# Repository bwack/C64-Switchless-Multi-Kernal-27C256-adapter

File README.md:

[![Badge License]][License]

<br>

![Logo]

<br>

<div align = center>

***A C64 + Disk Drives Switch-less Multi*** <br>
***Kernel ROM Adapter / Switcher***

<br>

---

[![Button Playlist]][Playlist]   
[![Button OSHPark]][OSHPark]   
[![Button Forum]][Forum]

[![Button Usage]][Usage]  
[![Button Develop]][Develop]  
[![Button Changelog]][Changelog]

---

<br>
<br>

<br>

## Supported Devices

![C64]  ![C64C]  ![1541]  ![1541C]  ![1541-II] 

<br>

</div>
  
<br>

## Boards

### Long

The  `longboard`  is designed for <br>
the  <kbd> C64 </kbd>  **+**  <kbd> 1541 </kbd>  **/**  <kbd> 1541Late </kbd>

<br>

### Short

The  `shortboard`  is designed for <br>
the  <kbd> C64C </kbd>  **+**  <kbd> 1541C </kbd>  **/**  <kbd> 1541-II </kbd>

<br>

### Note

*The innards of  `C64`  /  `C64C`  and  `1541`  /  `1541C`* <br>
*are often mixed together, and you must check their* <br>
*cases to be sure which boards they have.*

<br>
<br>

## Acknowledgment

### Based On   [<kbd> Sven Petersen </kbd>][Petersen]

*[C64 Kernal Adaptor Switch Shortboard]*

### Old Version   [<kbd> DiscoHR </kbd>][DiscoHR]

*[C64C C128 Multikernal Adapter]*

*It is possible to reused the original LED / Cable assembly.*

### Idea From   [<kbd> Tebl </kbd>][DiscoHR]

*[C64 Kernal Switcher]*

<br>

<!----------------------------------------------------------------------------->

[Playlist]: https://www.youtube.com/playlist?list=PLtQOf_JULmrQTB7486X5pXG1Aaxbl_RdE
[OSHPark]: https://oshpark.com/profiles/bwack 'Order The Board'
[Forum]: http://www.lemon64.com/forum/viewtopic.php?p=747333 'Lemon64 Forum Post'

[Changelog]: Documentation/Changelog.md
[Develop]: Documentation/Develop.md
[License]: LICENSE
[Usage]: Documentation/Usage.md
[Logo]: User%20Guide/media/SKS64-Logos-Ver2.png

[Badge License]: https://img.shields.io/badge/Open_Hardware-1.2-292961?style=for-the-badge

<!--------------------------------{ Devices }---------------------------------->

[1541-II]: https://img.shields.io/badge/１５４１－ＩＩ-d7cdbb?style=flat
[1541C]: https://img.shields.io/badge/１５４１Ｃ-d7cdbb?style=flat
[1541]: https://img.shields.io/badge/１５４１-d7cdbb?style=flat
[C64C]: https://img.shields.io/badge/Ｃ６４Ｃ-d7cdbb?style=flat
[C64]: https://img.shields.io/badge/Ｃ６４-d7cdbb?style=flat

<!----------------------------{ Acknowledgment }------------------------------->

[C64 Kernal Adaptor Switch Shortboard]: https://github.com/svenpetersen1965/C64-Kernal-Adaptor-Switch-short-board-
[C64C C128 Multikernal Adapter]: https://github.com/discoHR/C64C-C128-multikernal-adapter
[C64 Kernal Switcher]: https://github.com/tebl/C64-Kernal-Switcher

[Petersen]: https://github.com/svenpetersen1965
[DiscoHR]: https://github.com/discoHR
[Tebl]: https://github.com/tebl

<!--------------------------------{ Buttons }---------------------------------->

[Button Changelog]: https://img.shields.io/badge/Changelog-19abdd?style=for-the-badge&logoColor=white&logo=AzureArtifacts
[Button Playlist]: https://img.shields.io/badge/Playlist-FF0000?style=for-the-badge&logoColor=white&logo=Youtube
[Button Develop]: https://img.shields.io/badge/Develop-00979D?style=for-the-badge&logoColor=white&logo=Arduino
[Button OSHPark]: https://img.shields.io/badge/OSHPark-752c8d?style=for-the-badge&logoColor=white&logo=Houzz
[Button Usage]: https://img.shields.io/badge/Usage-ED145B?style=for-the-badge&logoColor=white&logo=AppleArcade
[Button Forum]: https://img.shields.io/badge/Forum-5287B8?style=for-the-badge&logoColor=white&logo=AskUbuntu

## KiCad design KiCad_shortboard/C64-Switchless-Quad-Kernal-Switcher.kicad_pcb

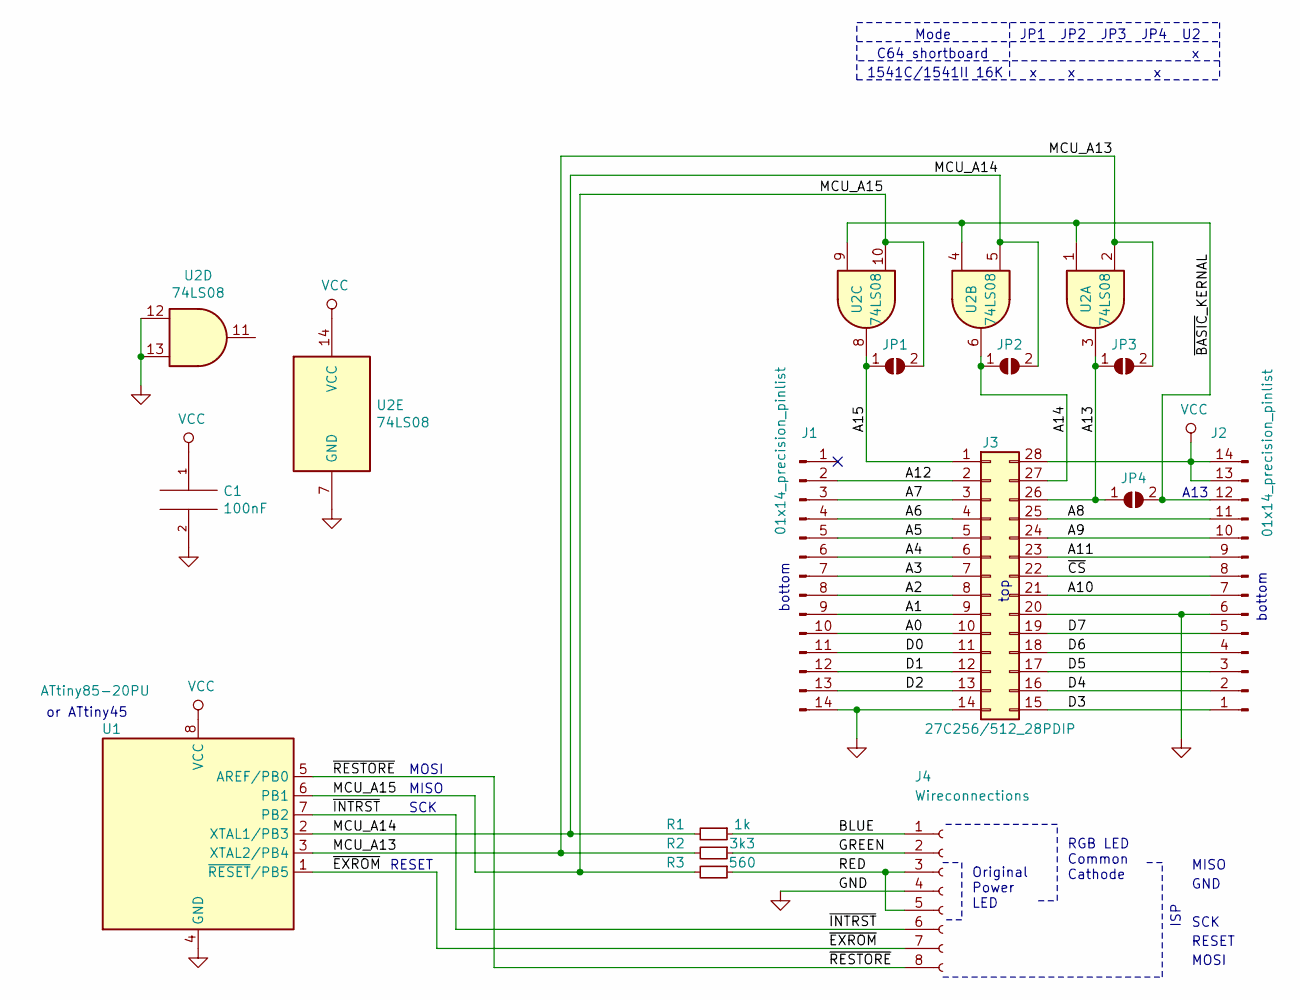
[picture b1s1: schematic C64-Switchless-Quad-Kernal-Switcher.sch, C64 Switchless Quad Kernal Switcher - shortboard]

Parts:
C1: 100nF; R_0805_2012Metric_Pad1.15x1.40mm_HandSolder
J1, J2: 01x14_precision_pinlist; PinHeader_1x14_P2.54mm_Vertical
J3: 27C256/512_28PDIP; DIP-28_W15.24mm_Socket
J4: Wireconnections; PinHeader_1x08_P2.54mm_Horizontal
JP1, JP2, JP3, JP4: SolderJumper_2_Open; J_0402
R1: 1k; R_0805_2012Metric_Pad1.15x1.40mm_HandSolder
R2: 3k3; R_0805_2012Metric_Pad1.15x1.40mm_HandSolder
R3: 560; R_0805_2012Metric_Pad1.15x1.40mm_HandSolder
U1: ATtiny85-20PU; DIP-8_W7.62mm_Socket
U2: 74LS08; SOIC-14_3.9x8.7mm_P1.27mm

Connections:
/A0: J1.10, J3.10
/A1: J1.9, J3.9
/A2: J1.8, J3.8
/A3: J1.7, J3.7
/A4: J1.6, J3.6
/A5: J1.5, J3.5
/A6: J1.4, J3.4
/A7: J1.3, J3.3
/A8: J2.11, J3.25
/A9: J2.10, J3.24
/A10: J2.7, J3.21
/A11: J2.9, J3.23
/A12: J1.2, J3.2
/A13: J3.26, JP3.1 (A), JP4.1 (A), U2.3
/A14: J3.27, JP2.1 (A), U2.6
/A15: J3.1, JP1.1 (A), U2.8
/BLUE: J4.1, R1.1
/D0: J1.11, J3.11
/D1: J1.12, J3.12
/D2: J1.13, J3.13
/D3: J2.1, J3.15
/D4: J2.2, J3.16
/D5: J2.3, J3.17
/D6: J2.4, J3.18
/D7: J2.5, J3.19
/GREEN: J4.2, R2.1
/MCU_A13: JP3.2 (B), R2.2, U1.3 (XTAL2/PB4), U2.2
/MCU_A14: JP2.2 (B), R1.2, U1.2 (XTAL1/PB3), U2.5
/MCU_A15: JP1.2 (B), R3.2, U1.6 (PB1), U2.10
/RED: J4.3, J4.5, R3.1
/~BASIC~_KERNAL: J2.12, JP4.2 (B), U2.1, U2.4, U2.9
/~CS~: J2.8, J3.22
/~EXROM~: J4.7, U1.1 (~RESET~/PB5)
/~INTRST~: J4.6, U1.7 (PB2)
/~RESTORE~: J4.8, U1.5 (AREF/PB0)
GND: C1.2, J1.14, J2.6, J3.14, J3.20, J4.4, U1.4 (GND), U2.7 (GND), U2.12, U2.13
VCC: C1.1, J2.13, J2.14, J3.28, U1.8 (VCC), U2.14 (VCC)

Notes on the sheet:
bottom
top
SCK
MISO
MOSI
RESET
Original Power LED
RGB LED Common Cathode
ISP
GND
or ATtiny45
A13
JP1 JP2 JP3 JP4 U2
C64 shortboard
Mode
1541C/1541II 16K

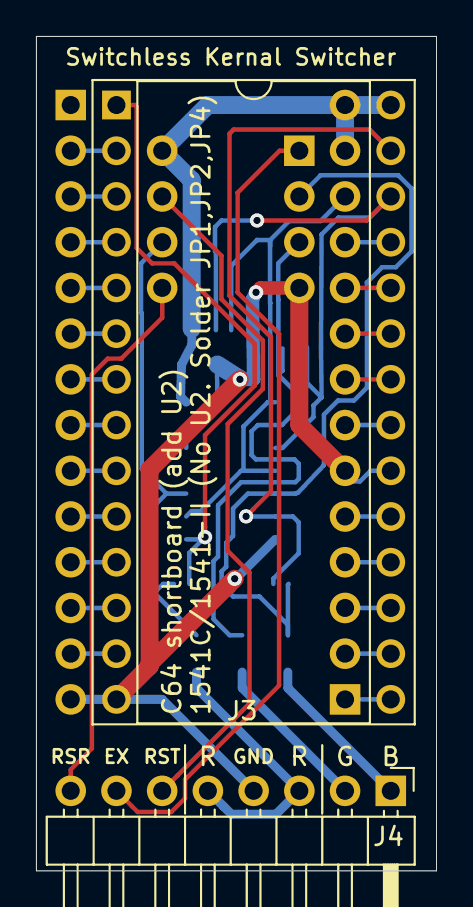
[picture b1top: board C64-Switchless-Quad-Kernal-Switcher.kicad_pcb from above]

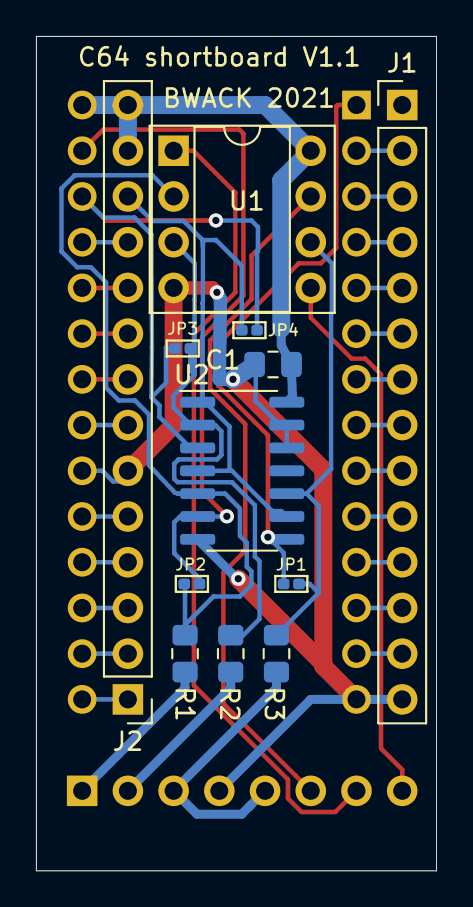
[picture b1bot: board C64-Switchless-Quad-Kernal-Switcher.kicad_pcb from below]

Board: 2 copper layers, 22.2 x 46.4 mm, 14 parts (12 on the bottom side), 37 nets.

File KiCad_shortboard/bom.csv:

Reference, Quantity, Value, Footprint, Datasheet
C1 ,1,"100nF","Resistor_SMD:R_0805_2012Metric_Pad1.15x1.40mm_HandSolder","~"
J2 J1 ,2,"01x14_precision_pinlist","Connector_PinHeader_2.54mm:PinHeader_1x14_P2.54mm_Vertical","~"
J3 ,1,"27C256/512_28PDIP","Package_DIP:DIP-28_W15.24mm_Socket","~"
J4 ,1,"Wireconnections","Connector_PinHeader_2.54mm:PinHeader_1x08_P2.54mm_Horizontal","~"
R1 ,1,"1k","Resistor_SMD:R_0805_2012Metric_Pad1.15x1.40mm_HandSolder","~"
R2 ,1,"3k3","Resistor_SMD:R_0805_2012Metric_Pad1.15x1.40mm_HandSolder","~"
R3 ,1,"560","Resistor_SMD:R_0805_2012Metric_Pad1.15x1.40mm_HandSolder","~"
U1 ,1,"ATtiny85-20PU","Package_DIP:DIP-8_W7.62mm_Socket","http://ww1.microchip.com/downloads/en/DeviceDoc/atmel-2586-a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"
U2 ,1,"74LS08","Package_SO:SOIC-14_3.9x8.7mm_P1.27mm","http://www.ti.com/lit/gpn/sn74LS08"

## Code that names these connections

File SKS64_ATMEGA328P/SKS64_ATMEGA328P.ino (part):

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//#define REDONLY

// I/O
#define RESTORE 8
#define RED 9
#define A13 10
#define A14 11
#define INTRST 7
#define EXROM 6

#define EEPROM_ADDRESS_MODE 1

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// state machine
#define STATE_INIT 4
#define STATE_SETUP 5
#define STATE_IDLE 0          // Stay in IDLE until RESTORE is held for 0.1s * PRESSTIME.
#define STATE_STILLHOLDING 1  // Continued holding RESTORE goto EXROMRESET, if released goto MENU.
#define STATE_MENU 2          // Single tap resets timeout and changes bank. Timeout goes to RESET.
#define STATE_RESET 3         // Resets machine and go back to IDLE.
#define STATE_EXROMRESET 7    // Resets machine with EXROM and go back to IDLE.
#define PRESSTIME 20   // Presstime in 0.1s to enter menu
#define HOLDTIME 30    // Press for PRESSTIME+HOLDTIME seconds to perform an EXROM-RESET
#define MENUTIMEOUT 20 // Timeout since last press of the restore in menu mode.
int state=STATE_INIT;
int next_state=STATE_INIT;

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  pinMode(RED, OUTPUT);
  pinMode(A13, OUTPUT);
  pinMode(A14, OUTPUT);
  pinMode(RESTORE, INPUT_PULLUP);
  pinMode(INTRST, INPUT);
  digitalWrite(RED, LOW);
  digitalWrite(A13, LOW);
  digitalWrite(A14, LOW);
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
  pinMode(EXROM, INPUT);
  digitalWrite(EXROM, HIGH);

  //ss.attachInterrupt( handleRxChar );
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 
        set_ledcolor(rom);
      }
      if (restore==0) counter=0;
      break;

    case STATE_RESET:
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      ss.ignore();
      ss.write(0xde);
      ss.write(rom);
      pinMode(INTRST, OUTPUT);
      digitalWrite(INTRST, LOW);
      delay(300);
      pinMode(INTRST, INPUT);
      ss.listen();
      EEPROM.write(0, rom&0x07);
      delay(5);
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      set_ledcolor(rom);
      next_state = STATE_IDLE;
      digitalWrite(INTRST, LOW);
      pinMode(INTRST, OUTPUT);
      delay(100);

      pinMode(EXROM, OUTPUT);
      digitalWrite(EXROM, LOW);
      delay(300);
      
      pinMode(INTRST, INPUT);
      digitalWrite(INTRST, HIGH);
      delay(100);

      pinMode(EXROM, INPUT);
      digitalWrite(EXROM, HIGH);
      EEPROM.write(0, rom&0x07);
      delay(300);
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
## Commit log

2016-08-20 :boom::camel: Added .gitattributes
2016-08-20 first commit
    my first commit
2016-08-20 PDF file added
    Note that this 555 based design is not completed.
2016-08-20 Optional MCU
    The MCU is optional in the 555 design. I added the footprint because
    space was available. Not finished.
2016-08-22 555 based: updated R2,R3. Added revision.
2016-08-22 Revision + silkscreen text
2016-09-08 swapped LED and RESTORE on GP2 and GP3
    GP3 is the fekken input only pin
2016-09-08 Rev 1.1 of the microcontroller files
2016-09-09 We need a README file
2016-09-09 added instant select-mode from reset button (discobranch)
2016-09-10 Sch+Layout changed to match RGB LEDs pinout
    See readme.txt
2016-09-10 Rev 1.11 Silkscreen, RGB LED
2016-09-10 silkscreen was on wrong layer - move 555 version
2016-09-10 Bill of materials
2016-09-16 disable eeprom at debug time
2016-09-16 removed kernal=0 and using switch-case block
2016-09-17 gitignore and hex file.
2016-09-17 hexfile
2016-09-17 project file
2016-09-17 LICENSE
2016-09-17 updated with license
2016-09-18 hole sizes
2016-09-19 mikroC config file
2016-09-28 Rev 1.13
    Moved IC2 to clear space for the socket in the C64.
2016-10-22 putting the mcu to sleep
2016-11-18 the hex-file i forgot to include
2017-10-02 Added support for PIC12F675
2017-10-08 The very early planning for the User Guide
2017-10-09 The beginning of a User Guide
2017-11-10 documentation still at a very early stage
2017-11-19 Documented the LED assembly and overview.
    PDF is old.
2018-05-06 Minor change.
2019-05-16 Added assembly instructions in the manual
2019-05-16 resistor values
2019-06-22 schematics and layout in user guide
2019-06-22 README rename
2019-06-22 Rename README to README.md
2019-06-23 Link to tebl's repository
2019-07-14 V1.20
2019-07-14 3d images
2019-07-15 User Guide
    not finished
2019-07-15 Via locations on longboard motherboards
2019-07-15 typo
2019-07-17 firmware updates: use eprom, exromreset, opencollector
    opencollector-ish means set reset and exrom as input when inactive.
2019-07-17 User Guide
2019-07-18 Update readme.md, shortboard version
2019-07-18 Preparing for shortboard version
2019-07-18 User Guide. Soldering instructions
2019-07-18 Update SKS64_SKETCH.ino
    still a bit buggy
2019-07-19 Firmware: Setup menu, motherboard and no. banks stored on eprom, small bugfixes
    Only need one firmware for all the possible usage types
    longboard, shortboard, 4 banks, 8 banks.
2019-07-20 User Guide update, the firmware.
2019-07-20 shortboard version not tested
2019-07-20 Don't rotate setup when entering setup menu
2019-07-21 Readme, 250469 wiring, user guide
2019-07-22 removed delays in setup, sleepmode when idle,
2019-07-23 longboard pcb version, 8 bank support
2019-07-24 shortboard version schematics added to user guide
2019-07-24 RED turned on after EXROM reset (flashcounter not zero)
2019-08-12 Updated BOM shortboard in User Guide. Added mouserproject link
2019-08-13 User Guide updated. 8 kernals in v1.21 confirmed working.
2020-04-13 Added the old PIC12F hex files again
2021-01-06 Set EXROM to input on startup instead of output - otherwise EXROM is held high until first reboot
2021-05-02 Firmware 1.2
2021-05-03 Removed led flashing delay at start of program. The flashing caused C64C to not warm start.
2021-05-03 Updated User Guide. Make it clearer to select fusebits.
2021-07-27 1.4 fixed: A15 always 0 at cold boot in 8 banks longboard mode
2021-08-10 1541C support in firmware and SKS64 shortboard pcb version
2021-08-10 firmware: removed startup delay (1s) causing startup issues
2021-08-10 Documentation update includes 1541
2021-10-19 build makefiles for making the four firmware variants
2022-04-03 The arduino code ported to atmega328p (arduino uno)
2022-05-28 Moved Changelog Into Dedicated File
2022-05-28 Added Quicklink
2022-05-28 Added More Quicklinks
2022-05-28 Added License Badge
2022-05-28 Adjusted Spacing
2022-05-28 Formatted Changelog
2022-05-28 Adjusted Formatting
2022-05-29 Formatted Supported Devices
2022-05-29 Moved Usage & Develop Into Dedicated Files
2022-05-29 Moved Usage & ...
2022-05-29 Formatted Acknowledgment
2022-05-29 Formatted Boards Section
2022-05-29 Formatted Develop
2022-05-29 Formatted Usage
